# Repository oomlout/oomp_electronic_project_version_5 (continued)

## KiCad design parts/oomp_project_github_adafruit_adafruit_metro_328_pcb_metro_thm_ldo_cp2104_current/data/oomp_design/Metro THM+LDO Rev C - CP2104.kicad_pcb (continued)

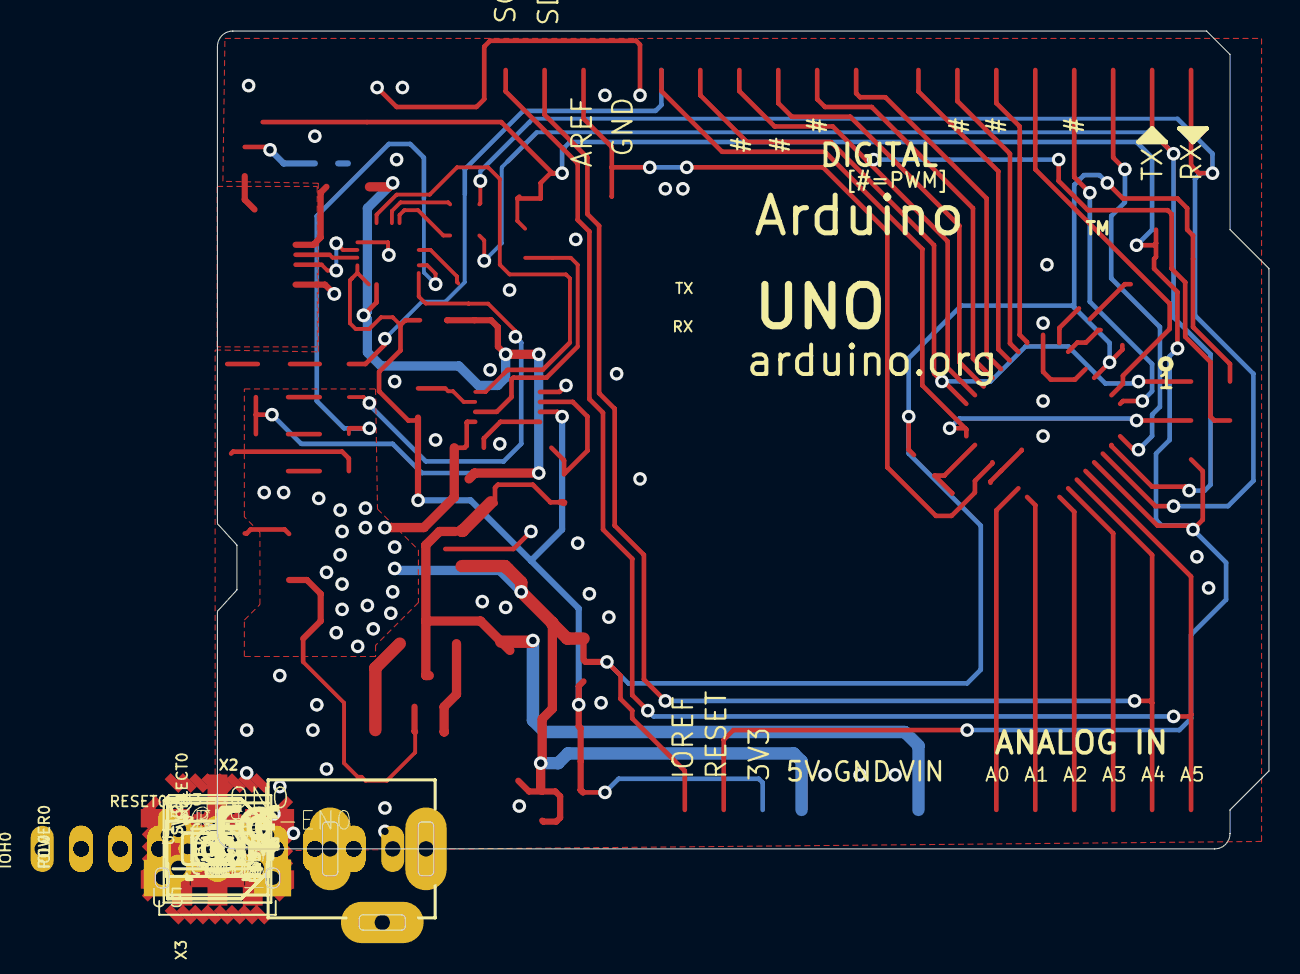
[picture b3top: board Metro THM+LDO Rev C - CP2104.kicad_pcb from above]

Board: 2 copper layers, 72.6 x 58.6 mm, 69 parts (1 on the bottom side), 53 nets.

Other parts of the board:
U$4: METROSILK_CP2104_TOP
U$14: METROSILK_BOT
U$15: PCBFEAT-REV-040
U$16: SYMBOL_FCC_TINY
U$17: SYMBOL_CE_TINY
UNK_HOLE_0: dummyfp0
UNK_HOLE_1: dummyfp1
UNK_HOLE_2: dummyfp2
UNK_HOLE_3: dummyfp3

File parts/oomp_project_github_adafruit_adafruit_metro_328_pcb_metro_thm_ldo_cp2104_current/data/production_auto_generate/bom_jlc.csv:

Comment,Designator,Footprint,LCSC Part #
,JP1,Metro THM+LDO Rev C - CP2104-import-fps:1X01_ROUND,C7501259
,X2,Metro THM+LDO Rev C - CP2104-import-fps:DCJACK_2MM_PTH,
,U$14,Metro THM+LDO Rev C - CP2104-import-fps:METROSILK_BOT,
,U$4,Metro THM+LDO Rev C - CP2104-import-fps:METROSILK_CP2104_TOP,
,U$15,Metro THM+LDO Rev C - CP2104-import-fps:PCBFEAT-REV-040,
,GROUND1,Metro THM+LDO Rev C - CP2104-import-fps:SJ,
,VSELECT0,Metro THM+LDO Rev C - CP2104-import-fps:SOLDERJUMPER_2WAY_OPEN_NOPASTE,
,RESET-EN0,Metro THM+LDO Rev C - CP2104-import-fps:SOLDERJUMPER_CLOSEDWIRE,
,SW2,Metro THM+LDO Rev C - CP2104-import-fps:SPDT_SMT_SSSS811101,
,U$17,Metro THM+LDO Rev C - CP2104-import-fps:SYMBOL_CE_TINY,
,U$16,Metro THM+LDO Rev C - CP2104-import-fps:SYMBOL_FCC_TINY,
0.1uF,"C2,C4,C5,C6,C9,C12,C13,C15",Metro THM+LDO Rev C - CP2104-import-fps:0805-NO,
0.1uF,C10,Metro THM+LDO Rev C - CP2104-import-fps:0805_10MGAP,
10K,"R7,R13,R14,R15,R16",Metro THM+LDO Rev C - CP2104-import-fps:0805-NO,C17414
10K,R8,Metro THM+LDO Rev C - CP2104-import-fps:_0805MP,C17414
10uF,"C1,C3,C7",Metro THM+LDO Rev C - CP2104-import-fps:0805-NO,
1K,"R1,R3,R6,R9,R10,R11,R12",Metro THM+LDO Rev C - CP2104-import-fps:0805-NO,C17513
1N4148,D2,Metro THM+LDO Rev C - CP2104-import-fps:SOD-323,
20329,X3,Metro THM+LDO Rev C - CP2104-import-fps:4UCONN_20329_V2,
20609,AD0,Metro THM+LDO Rev C - CP2104-import-fps:1X06_OVAL,C37208
20610,"IOL0,POWER0",Metro THM+LDO Rev C - CP2104-import-fps:1X08_OVAL,C492421
20611,IOH0,Metro THM+LDO Rev C - CP2104-import-fps:1X10_OVAL,C57369
3x2 M,ICSP0,Metro THM+LDO Rev C - CP2104-import-fps:2X03_ROUND_70MIL,
47uF+/6.3V+,PC2,Metro THM+LDO Rev C - CP2104-import-fps:PANASONIC_D,
47uF/25V,PC1,Metro THM+LDO Rev C - CP2104-import-fps:PANASONIC_D,
500mA,F2,Metro THM+LDO Rev C - CP2104-import-fps:1206-NO,
6mm,RESET0,Metro THM+LDO Rev C - CP2104-import-fps:EVQ-Q2,
AP2112-3.3,U4,Metro THM+LDO Rev C - CP2104-import-fps:SOT23-5,
ATMEGA328P-AU,ZU4,Metro THM+LDO Rev C - CP2104-import-fps:TQFP32-08,
CP2104,U3,Metro THM+LDO Rev C - CP2104-import-fps:QFN24_4MM_SMSC,
CSTCE16M0V53-R0 16MHZ,Y2,Metro THM+LDO Rev C - CP2104-import-fps:RESONATOR,
DMP3098L,"T1,T2",Metro THM+LDO Rev C - CP2104-import-fps:SOT-23,
FERRITE,"FB1,FB2",Metro THM+LDO Rev C - CP2104-import-fps:0805-NO,
FIDUCIAL_1MM,"FD1,FD2,FD3",Metro THM+LDO Rev C - CP2104-import-fps:FIDUCIAL_1MM,
GREEN,ON0,Metro THM+LDO Rev C - CP2104-import-fps:CHIPLED_0805_NOOUTLINE,
LMV358IDGKR,U5,Metro THM+LDO Rev C - CP2104-import-fps:MSOP08,
MBR120,D1,Metro THM+LDO Rev C - CP2104-import-fps:SOD-123,
NCP1117ST50T3G,U1,Metro THM+LDO Rev C - CP2104-import-fps:SOT223-R,
RED,L0,Metro THM+LDO Rev C - CP2104-import-fps:CHIPLED_0805_NOOUTLINE,
YELLOW,"RXLED0,TXLED0",Metro THM+LDO Rev C - CP2104-import-fps:CHIPLED_0805_NOOUTLINE,

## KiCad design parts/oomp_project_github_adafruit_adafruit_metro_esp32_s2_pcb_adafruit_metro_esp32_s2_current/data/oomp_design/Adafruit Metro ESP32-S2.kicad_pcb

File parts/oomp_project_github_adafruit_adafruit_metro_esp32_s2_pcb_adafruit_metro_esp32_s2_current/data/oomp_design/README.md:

# OOMP KiCad design copy

Open `Adafruit Metro ESP32-S2.kicad_pro` (or the `.kicad_pcb` / `.kicad_sch`) in KiCad. Local OOMP libraries are under `libraries/`. Original inputs are preserved in [../original/](../original/).

Only verified unchanged installed KiCad defaults were renamed. Modified, custom, unmatched and unavailable items remain unchanged. Soldering variants are never swapped during conversion. Existing pad coordinates, nets and UUIDs are preserved.

See [conversion_report.yaml](conversion_report.yaml) for every conversion and skip. Copy this directory before editing; regeneration refuses to overwrite edited design files.

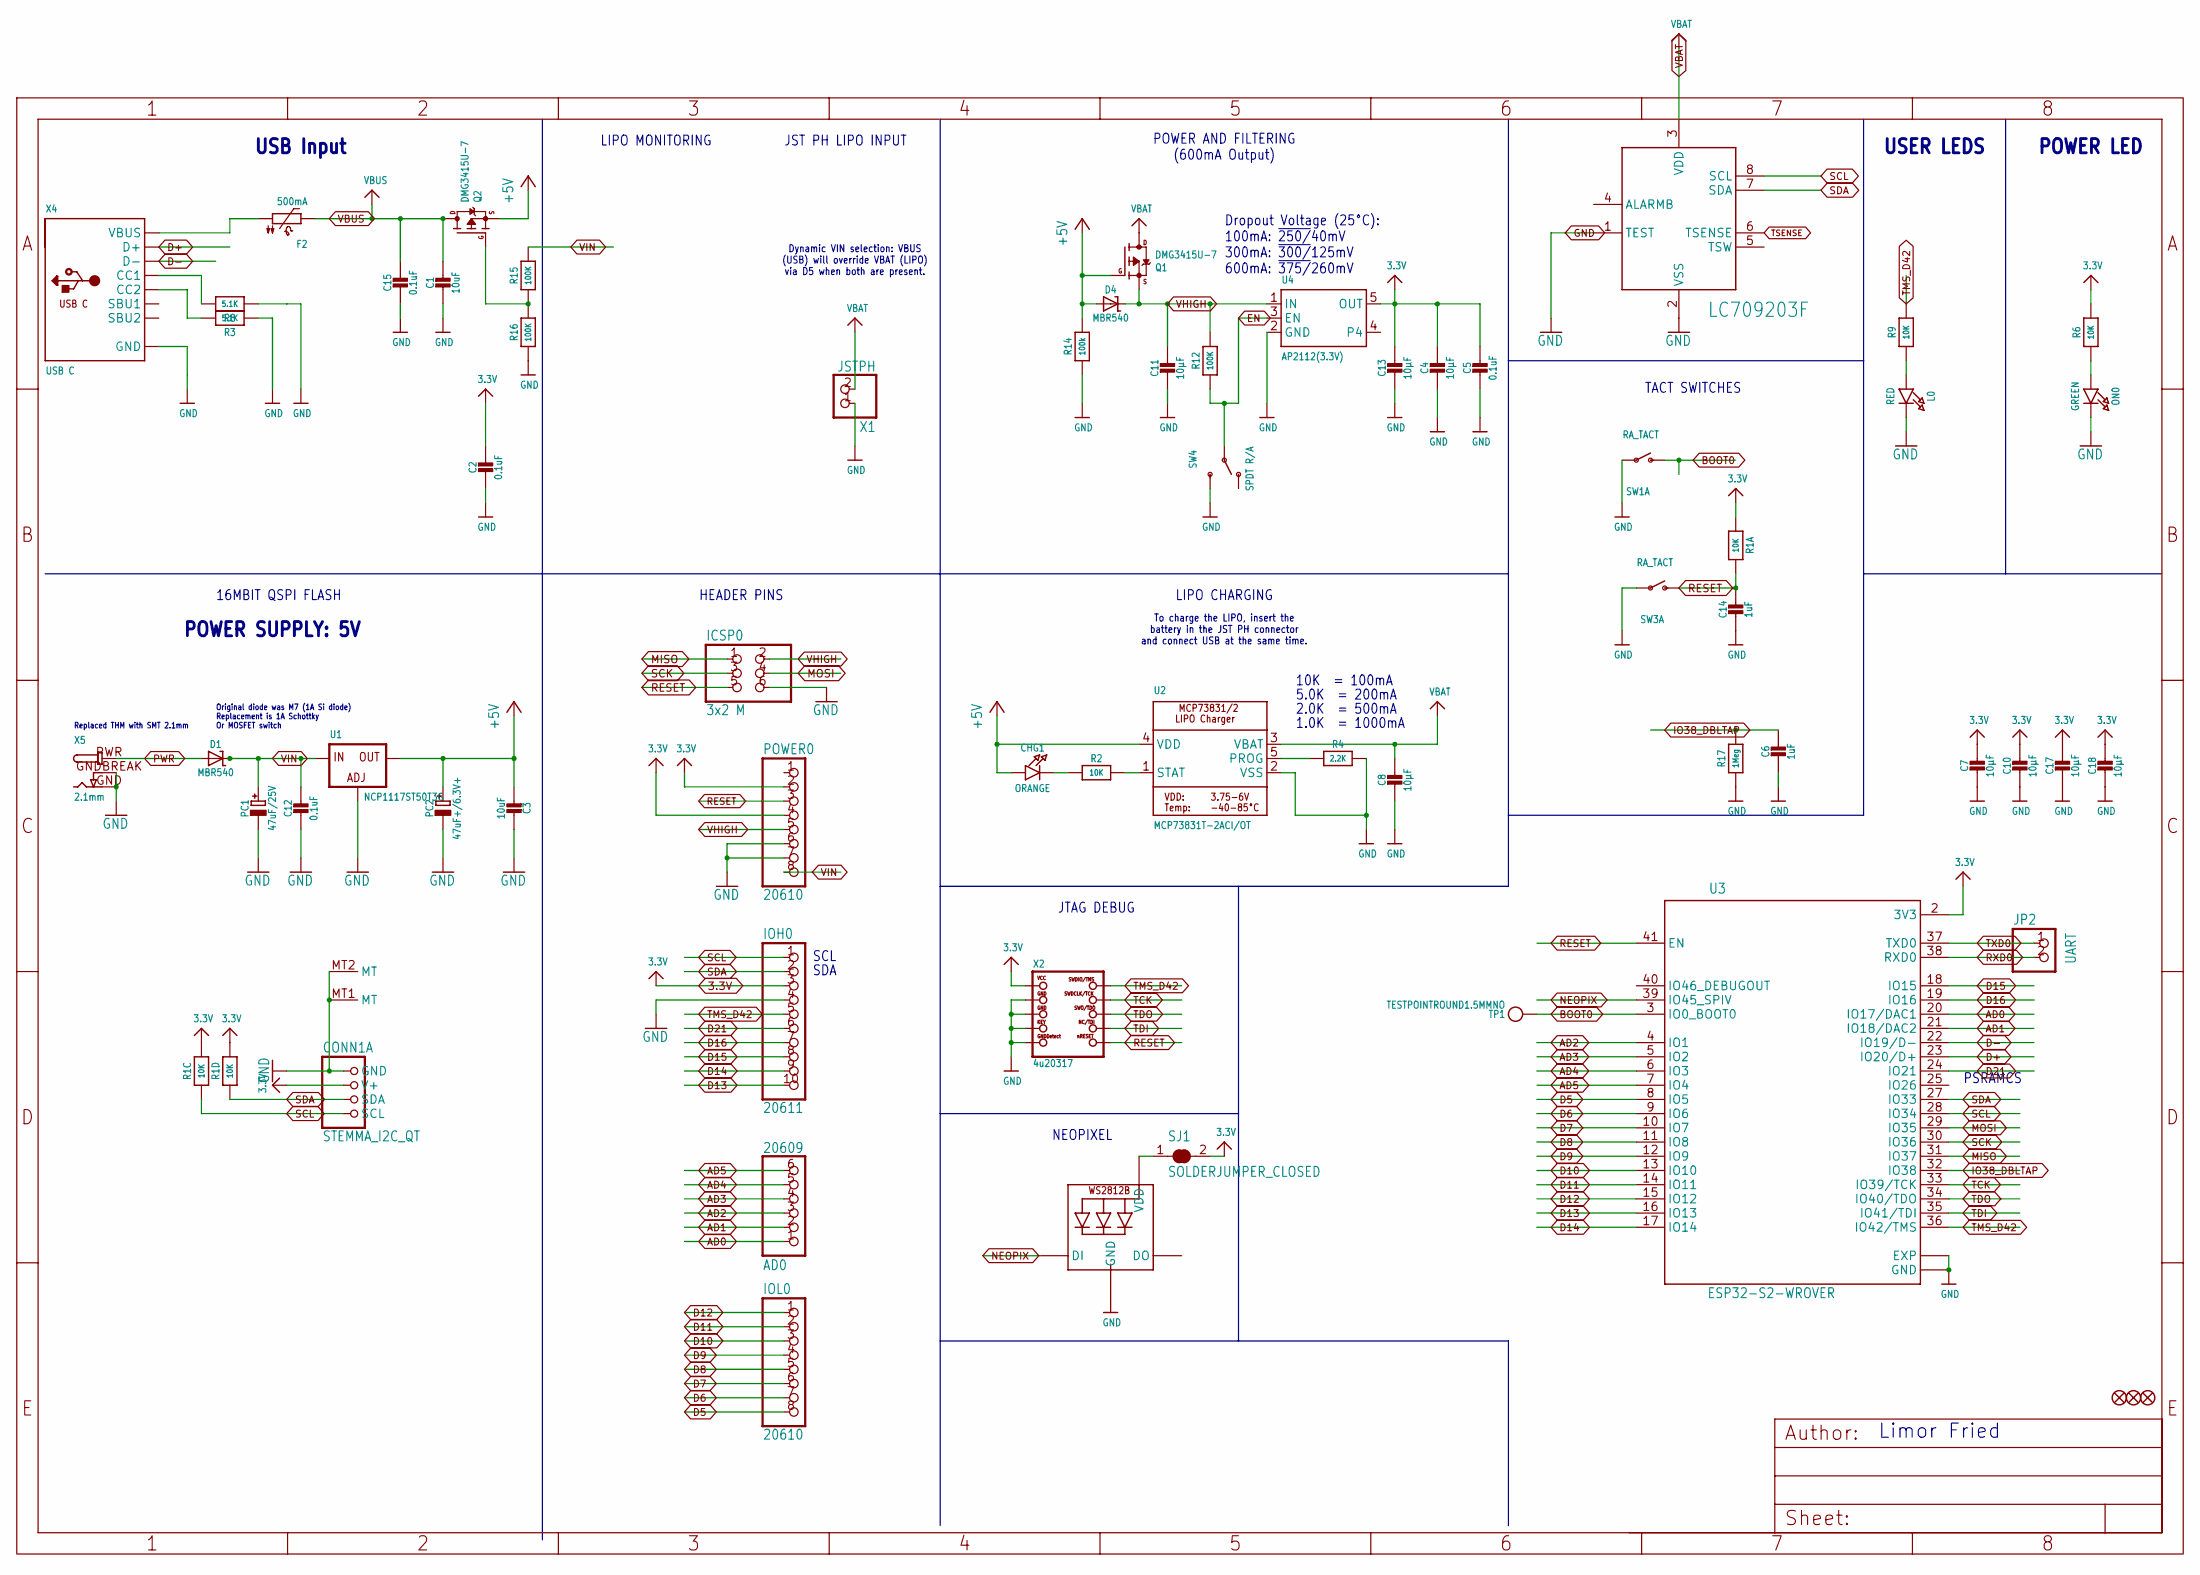
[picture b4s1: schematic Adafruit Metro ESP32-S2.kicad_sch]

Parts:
AD0: 20609; 1X06_OVALWAVE
C1, C3: 10uF; 0805-NO
C2, C5, C12, C15: 0.1uF; 0603-NO
C4, C7, C8, C10, C11, C13, C17, C18: 10µF; 0805-NO
C6, C14: 1uF; 0603-NO
CHG1: ORANGE; CHIPLED_0603_NOOUTLINE
CONN1: STEMMA_I2C_QT; JST_SH4
D1, D4: MBR540; SOD-123
F2: 500mA; 1206
FD1, FD2, FD3: FIDUCIAL_1MM
IC2: LC709203F; WDFN8_3X4_0.65
ICSP0: 3x2 M; 2X03_ROUND_70MIL
IOH0: 20611; 1X10_OVALWAVE
IOL0: 20610; 1X08_OVALWAVE
JP2: UART; 1X02_ROUND
L0: RED; CHIPLED_0603_NOOUTLINE
LED1: WS2812B3535; LED3535
ON0: GREEN; CHIPLED_0603_NOOUTLINE
PC1: 47uF/25V; PANASONIC_D
PC2: 47uF+/6.3V+; PANASONIC_D
POWER0: 20610; 1X08_OVALWAVE
Q1, Q2: DMG3415U-7; SOT23-R
R1: 10K; RESPACK_4X0603
R2, R6, R9: 10K; 0603-NO
R3, R8: 5.1K; 0603-NO
R4: 2.2K; 0603-NO
R12, R15, R16: 100K; 0603-NO
R14: 100k; 0603-NO
R17: 1Meg; 0603-NO
SJ1: SOLDERJUMPER_CLOSED; SOLDERJUMPER_CLOSEDWIRE
SW1, SW3: RA_TACT; SPST_TACTILE_RA
SW4: SPDT R/A; SPDT_SMT_SSSS811101
TP1: TESTPOINTROUND1.5MMNO; TESTPOINT_ROUND_1.5MM_NO
U1: NCP1117ST50T3G; SOT223-R
U2: MCP73831T-2ACI/OT; SOT23-5
U3: ESP32-S2-WROVER; MODULE_ESP32-S2-WROVER
U4: AP2112(3.3V); SOT23-5
X1: JSTPH; JSTPH2_BATT
X2: 4u20317; 2X05_1.27MM_BOX_POSTS
X4: USB C; USB_C_CUSB31-CFM2AX-01-X
X5: 2.1mm; DCJACK_2MM_PTH

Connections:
3.3V: C2.1, C4.1, C5.1, C7.1, C10.1, C13.1, C17.1, C18.1, CONN1.2 (V+), IOH0.3, POWER0.2, POWER0.4, R1.1, R1.5 (2), R1.6 (2), R6.2, SJ1.2, U3.2 (3V3), U4.5 (OUT), X2.1 (VCC)
+5V: C3.2, CHG1.A, D4.A, PC2.+, Q1.1 (G), Q2.2 (S), R14.2, U1.2 (OUT), U1.4 (OUT), U2.4 (VDD)
AD0: AD0.1, U3.20 (IO17/DAC1)
AD1: AD0.2, U3.21 (IO18/DAC2)
AD2: AD0.3, U3.4 (IO1)
AD3: AD0.4, U3.5 (IO2)
AD4: AD0.5, U3.6 (IO3)
AD5: AD0.6, U3.7 (IO4)
BOOT0: SW1.2 (S), TP1.P$1, U3.3 (IO0_BOOT0)
D5: IOL0.8, U3.8 (IO5)
D6: IOL0.7, U3.9 (IO6)
D7: IOL0.6, U3.10 (IO7)
D8: IOL0.5, U3.11 (IO8)
D9: IOL0.4, U3.12 (IO9)
D10: IOL0.3, U3.13 (IO10)
D11: IOL0.2, U3.14 (IO11)
D12: IOL0.1, U3.15 (IO12)
D13: IOH0.10, U3.16 (IO13)
D14: IOH0.9, U3.17 (IO14)
D15: IOH0.8, U3.18 (IO15)
D16: IOH0.7, U3.19 (IO16)
D21: IOH0.6, U3.24 (IO21)
D+: U3.23 (IO20/D+), X4.A6 (D+), X4.B6 (D+)
D-: U3.22 (IO19/D-), X4.A7 (D-), X4.B7 (D-)
EN: R12.1, SW4.B, U4.3 (EN)
GND: C1.2, C2.2, C3.1, C4.2, C5.2, C6.2, C7.2, C8.2, C10.2, C11.2, C12.2, C13.2, C14.2, C15.2, C17.2, C18.2, CONN1.1 (GND), CONN1.MT1 (MT), CONN1.MT2 (MT), IC2.1 (TEST), IC2.2 (VSS), ICSP0.6, IOH0.4, L0.C, LED1.4 (GND), ON0.C, PC1.-, PC2.-, POWER0.6, POWER0.7, R3.1, R4.2, R8.1, R14.1, R16.1, R17.1, SW1.1, SW3.1, SW4.C (S), U1.1 (ADJ), U2.2 (VSS), U3.1 (GND), U3.26 (GND), U3.42 (GND), U3.43_1 (EXP), U3.43_2 (EXP), U3.43_3 (EXP), U3.43_4 (EXP), U3.43_5 (EXP), U3.43_6 (EXP), U3.43_7 (EXP), U3.43_8 (EXP), U3.43_9 (EXP), U3.43_10 (EXP), U3.43_11 (EXP), U3.43_12 (EXP), U3.43_13 (EXP), U3.43_14 (EXP), U3.43_15 (EXP), U3.43_16 (EXP), U3.43_17 (EXP), U3.43_18 (EXP), U3.43_19 (EXP), U3.43_20 (EXP), U3.43_21 (EXP), U4.2 (GND), X1.1, X2.3 (GND), X2.5 (GND), X2.7 (KEY), X2.9 (GNDDETECT), X4.A1B12 (GND), X4.B1A12 (GND), X5.GND, X5.GNDBREAK
IO38_DBLTAP: C6.1, R17.2, U3.32 (IO38)
MISO: ICSP0.1, U3.31 (IO37)
MOSI: ICSP0.4, U3.29 (IO35)
unnamed: L0.A, R9.1
unnamed: Q2.1 (G), R15.1, R16.2
unnamed: ON0.A, R6.1
unnamed: CHG1.C, R2.1
unnamed: LED1.2 (VDD), SJ1.1
unnamed: R2.2, U2.1 (STAT)
unnamed: R8.2, X4.A5 (CC1)
unnamed: R3.2, X4.B5 (CC2)
unnamed: R4.1, U2.5 (PROG)
unnamed: F2.1, X4.A4B9 (VBUS), X4.B4A9 (VBUS)
NEOPIX: LED1.1 (DI), U3.39 (IO45_SPIV)
PWR: D1.A, X5.PWR
RESET: C14.1, ICSP0.5, POWER0.3, R1.8 (2), SW3.2 (S), U3.41 (EN), X2.10 (NRESET)
RXD0: JP2.2, U3.38 (RXD0)
SCK: ICSP0.3, U3.30 (IO36)
SCL: CONN1.4 (SCL), IC2.8 (SCL), IOH0.1, R1.3 (1), U3.28 (IO34)
SDA: CONN1.3 (SDA), IC2.7 (SDA), IOH0.2, R1.4 (1), U3.27 (IO33)
TCK: U3.33 (IO39/TCK), X2.4 (SWDCLK)
TDI: U3.35 (IO41/TDI), X2.8 (TDI)
TDO: U3.34 (IO40/TDO), X2.6 (SWO)
TMS_D42: IOH0.5, R9.2, U3.36 (IO42/TMS), X2.2 (SWDIO)
TXD0: JP2.1, U3.37 (TXD0)
VBAT: C8.1, IC2.3 (VDD), Q1.3 (D), U2.3 (VBAT), X1.2
VBUS: C1.1, C15.1, F2.2, Q2.3 (D)
VHIGH: C11.1, D4.C, ICSP0.2, POWER0.5, Q1.2 (S), R12.2, U4.1 (IN)
VIN: C12.1, D1.C, PC1.+, POWER0.8, R15.2, U1.3 (IN)

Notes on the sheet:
16MBIT QSPI FLASH
POWER AND FILTERING (600mA Output)
PSRAMCS
POWER LED
Original diode was M7 (1A Si diode) Replacement is 1A Schottky Or MOSFET switch
JST PH LIPO INPUT
1.0K = 1000mA
Limor Fried
SDA
NEOPIXEL
To charge the LIPO, insert the battery in the JST PH connector and connect USB at the same time.
LIPO MONITORING
SCL
USB Input
Replaced THM with SMT 2.1mm
Dropout Voltage (25°C): 100mA: ~{250/}40mV 300mA: ~{300/}125mV 600mA: ~{375/}260mV
POWER SUPPLY: 5V
JTAG DEBUG
10K = 100mA
HEADER PINS
2.0K = 500mA
Dynamic VIN selection: VBUS (USB) will override VBAT (LIPO) via D5 when both are present.
5.0K = 200mA
TACT SWITCHES
USER LEDS
LIPO CHARGING

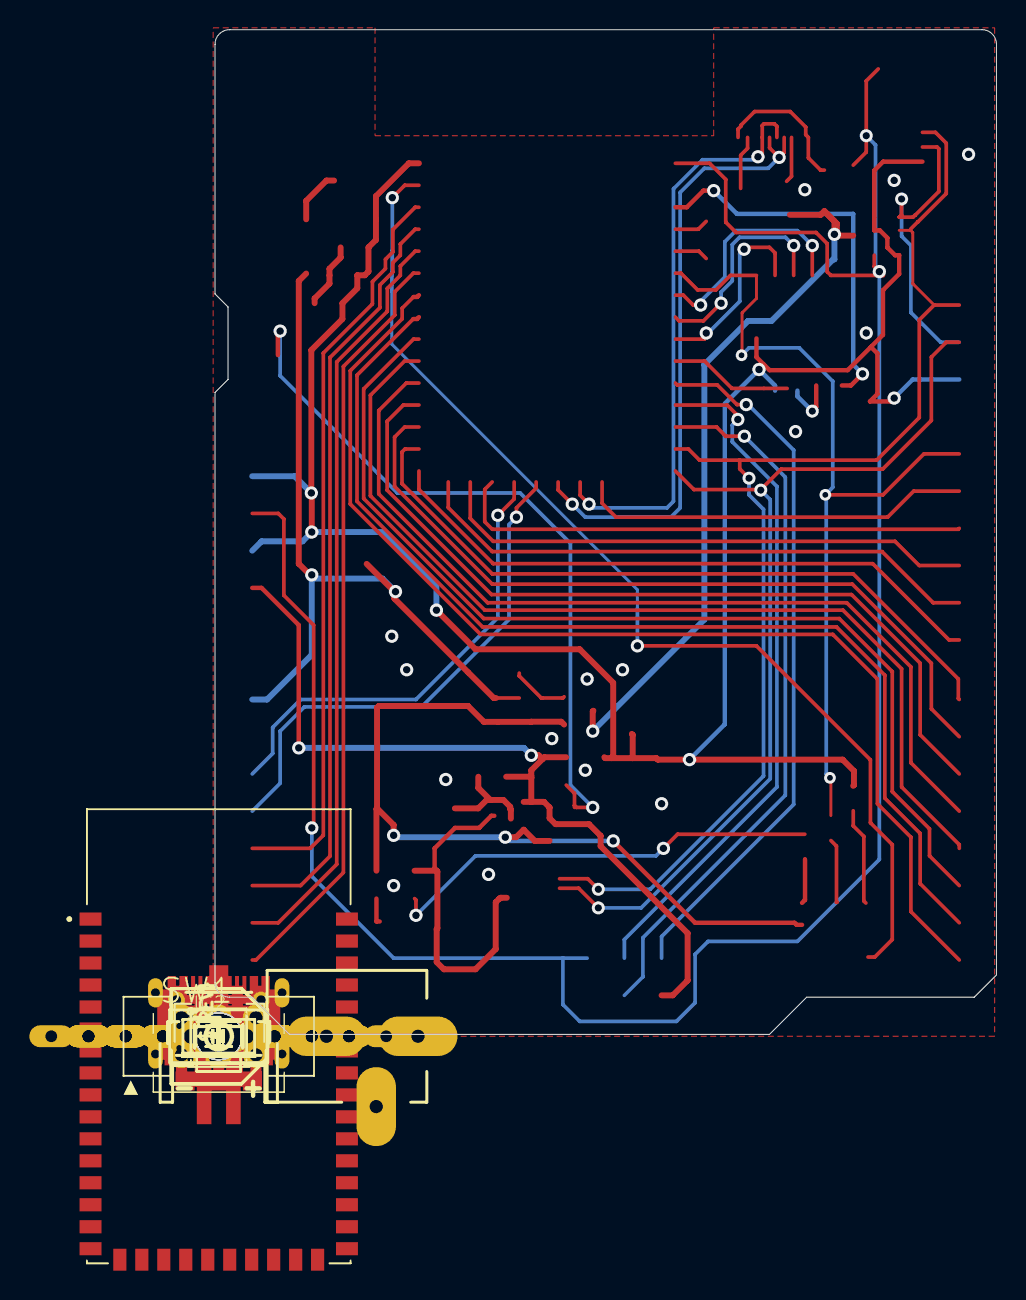
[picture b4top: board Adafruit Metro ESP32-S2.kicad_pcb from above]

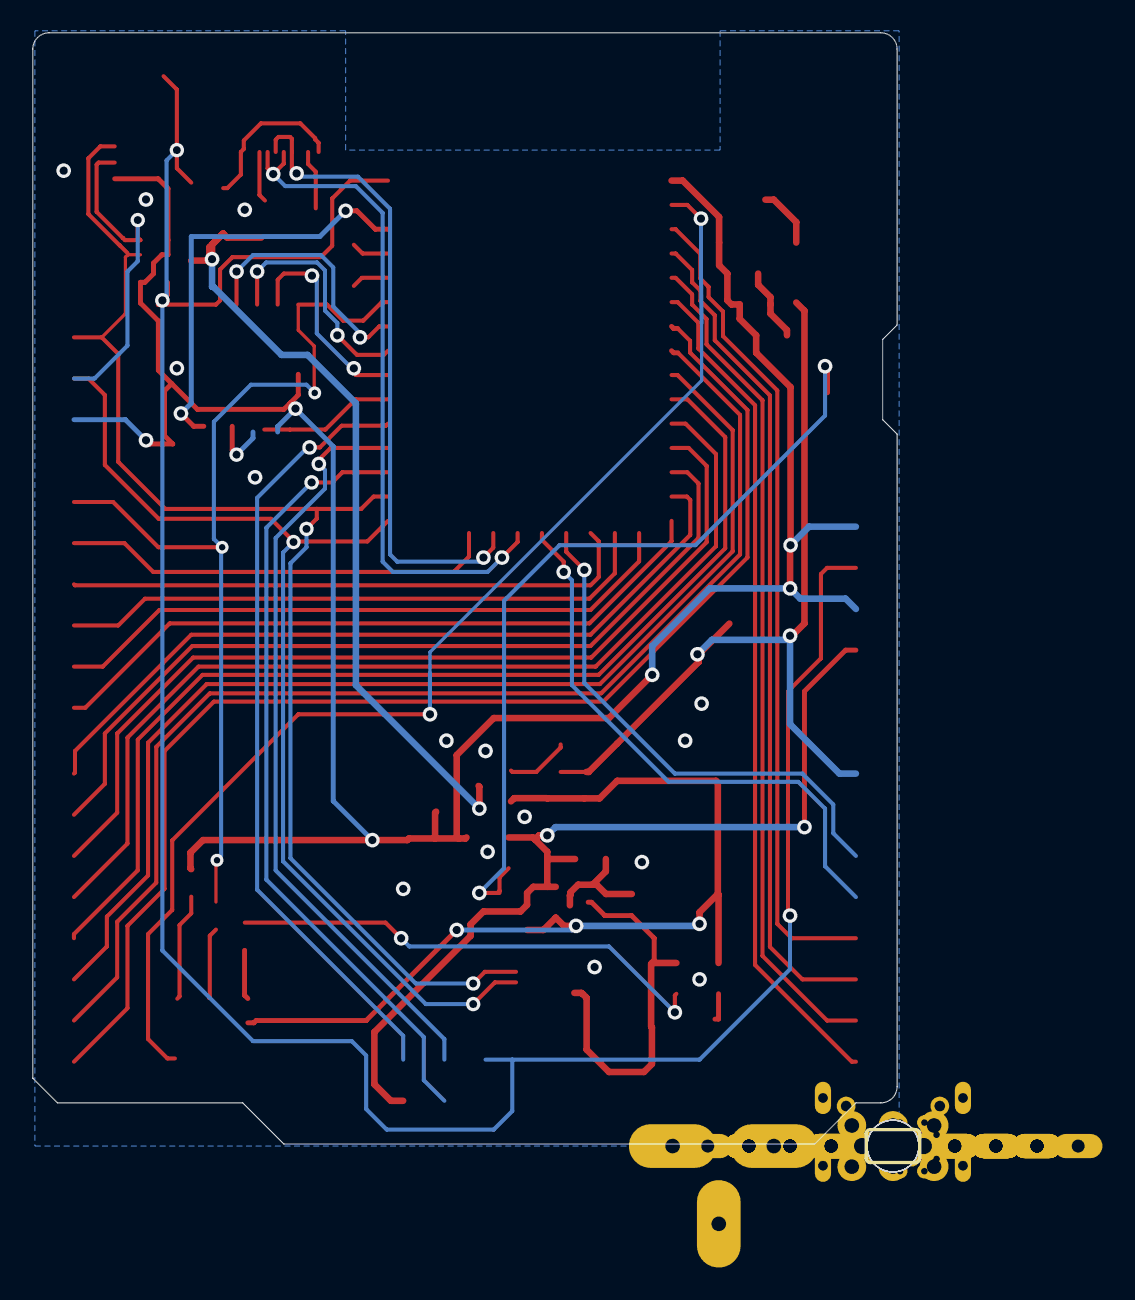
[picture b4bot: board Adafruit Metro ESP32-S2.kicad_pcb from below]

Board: 2 copper layers, 53.3 x 68.6 mm, 70 parts (3 on the bottom side), 55 nets.

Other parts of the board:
U$15: PCBFEAT-REV-040
U$52: ESP32S2_TOP
U$53: ESP32S2_BOT
UNK_HOLE_0: dummyfp0
UNK_HOLE_1: dummyfp1
UNK_HOLE_2: dummyfp2
UNK_HOLE_3: dummyfp3

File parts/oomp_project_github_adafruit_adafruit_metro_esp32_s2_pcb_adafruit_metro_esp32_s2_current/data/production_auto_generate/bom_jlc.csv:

Comment,Designator,Footprint,LCSC Part #
,U$53,Adafruit Metro ESP32-S2-import-fps:ESP32S2_BOT,
,U$52,Adafruit Metro ESP32-S2-import-fps:ESP32S2_TOP,
,U$15,Adafruit Metro ESP32-S2-import-fps:PCBFEAT-REV-040,
,TP1,Adafruit Metro ESP32-S2-import-fps:TESTPOINT_ROUND_1.5MM_NO,
0.1uF,"C2,C5,C12,C15",Adafruit Metro ESP32-S2-import-fps:0603-NO,C14663
100K,"R12,R15,R16",Adafruit Metro ESP32-S2-import-fps:0603-NO,C25803
100k,R14,Adafruit Metro ESP32-S2-import-fps:0603-NO,C25803
10K,"R2,R6,R9",Adafruit Metro ESP32-S2-import-fps:0603-NO,C98220
10K,R1,Adafruit Metro ESP32-S2-import-fps:RESPACK_4X0603,C98220
10uF,"C1,C3",Adafruit Metro ESP32-S2-import-fps:0805-NO,
10µF,"C4,C7,C8,C10,C11,C13,C17,C18",Adafruit Metro ESP32-S2-import-fps:0805-NO,
1Meg,R17,Adafruit Metro ESP32-S2-import-fps:0603-NO,C2907003
1uF,"C6,C14",Adafruit Metro ESP32-S2-import-fps:0603-NO,C5673
2.1mm,X5,Adafruit Metro ESP32-S2-import-fps:DCJACK_2MM_PTH,
2.2K,R4,Adafruit Metro ESP32-S2-import-fps:0603-NO,C4190
20609,AD0,Adafruit Metro ESP32-S2-import-fps:1X06_OVALWAVE,C37208
20610,"IOL0,POWER0",Adafruit Metro ESP32-S2-import-fps:1X08_OVALWAVE,C492421
20611,IOH0,Adafruit Metro ESP32-S2-import-fps:1X10_OVALWAVE,C57369
3x2 M,ICSP0,Adafruit Metro ESP32-S2-import-fps:2X03_ROUND_70MIL,
47uF+/6.3V+,PC2,Adafruit Metro ESP32-S2-import-fps:PANASONIC_D,
47uF/25V,PC1,Adafruit Metro ESP32-S2-import-fps:PANASONIC_D,
4u20317,X2,Adafruit Metro ESP32-S2-import-fps:2X05_1.27MM_BOX_POSTS,
5.1K,"R3,R8",Adafruit Metro ESP32-S2-import-fps:0603-NO,C23186
500mA,F2,Adafruit Metro ESP32-S2-import-fps:1206,
AP2112(3.3V),U4,Adafruit Metro ESP32-S2-import-fps:SOT23-5,
DMG3415U-7,"Q1,Q2",Adafruit Metro ESP32-S2-import-fps:SOT23-R,
ESP32-S2-WROVER,U3,Adafruit Metro ESP32-S2-import-fps:MODULE_ESP32-S2-WROVER,
FIDUCIAL_1MM,"FD1,FD2,FD3",Adafruit Metro ESP32-S2-import-fps:FIDUCIAL_1MM,
GREEN,ON0,Adafruit Metro ESP32-S2-import-fps:CHIPLED_0603_NOOUTLINE,
JSTPH,X1,Adafruit Metro ESP32-S2-import-fps:JSTPH2_BATT,
LC709203F,IC2,Adafruit Metro ESP32-S2-import-fps:WDFN8_3X4_0.65,
MBR540,"D1,D4",Adafruit Metro ESP32-S2-import-fps:SOD-123,
MCP73831T-2ACI/OT,U2,Adafruit Metro ESP32-S2-import-fps:SOT23-5,
NCP1117ST50T3G,U1,Adafruit Metro ESP32-S2-import-fps:SOT223-R,
ORANGE,CHG1,Adafruit Metro ESP32-S2-import-fps:CHIPLED_0603_NOOUTLINE,
RA_TACT,"SW1,SW3",Adafruit Metro ESP32-S2-import-fps:SPST_TACTILE_RA,
RED,L0,Adafruit Metro ESP32-S2-import-fps:CHIPLED_0603_NOOUTLINE,
SPDT R/A,SW4,Adafruit Metro ESP32-S2-import-fps:SPDT_SMT_SSSS811101,
STEMMA_I2C_QT,CONN1,Adafruit Metro ESP32-S2-import-fps:JST_SH4,C160404
UART,JP2,Adafruit Metro ESP32-S2-import-fps:1X02_ROUND,C492401
USB C,X4,Adafruit Metro ESP32-S2-import-fps:USB_C_CUSB31-CFM2AX-01-X,
WS2812B3535,LED1,Adafruit Metro ESP32-S2-import-fps:LED3535,
